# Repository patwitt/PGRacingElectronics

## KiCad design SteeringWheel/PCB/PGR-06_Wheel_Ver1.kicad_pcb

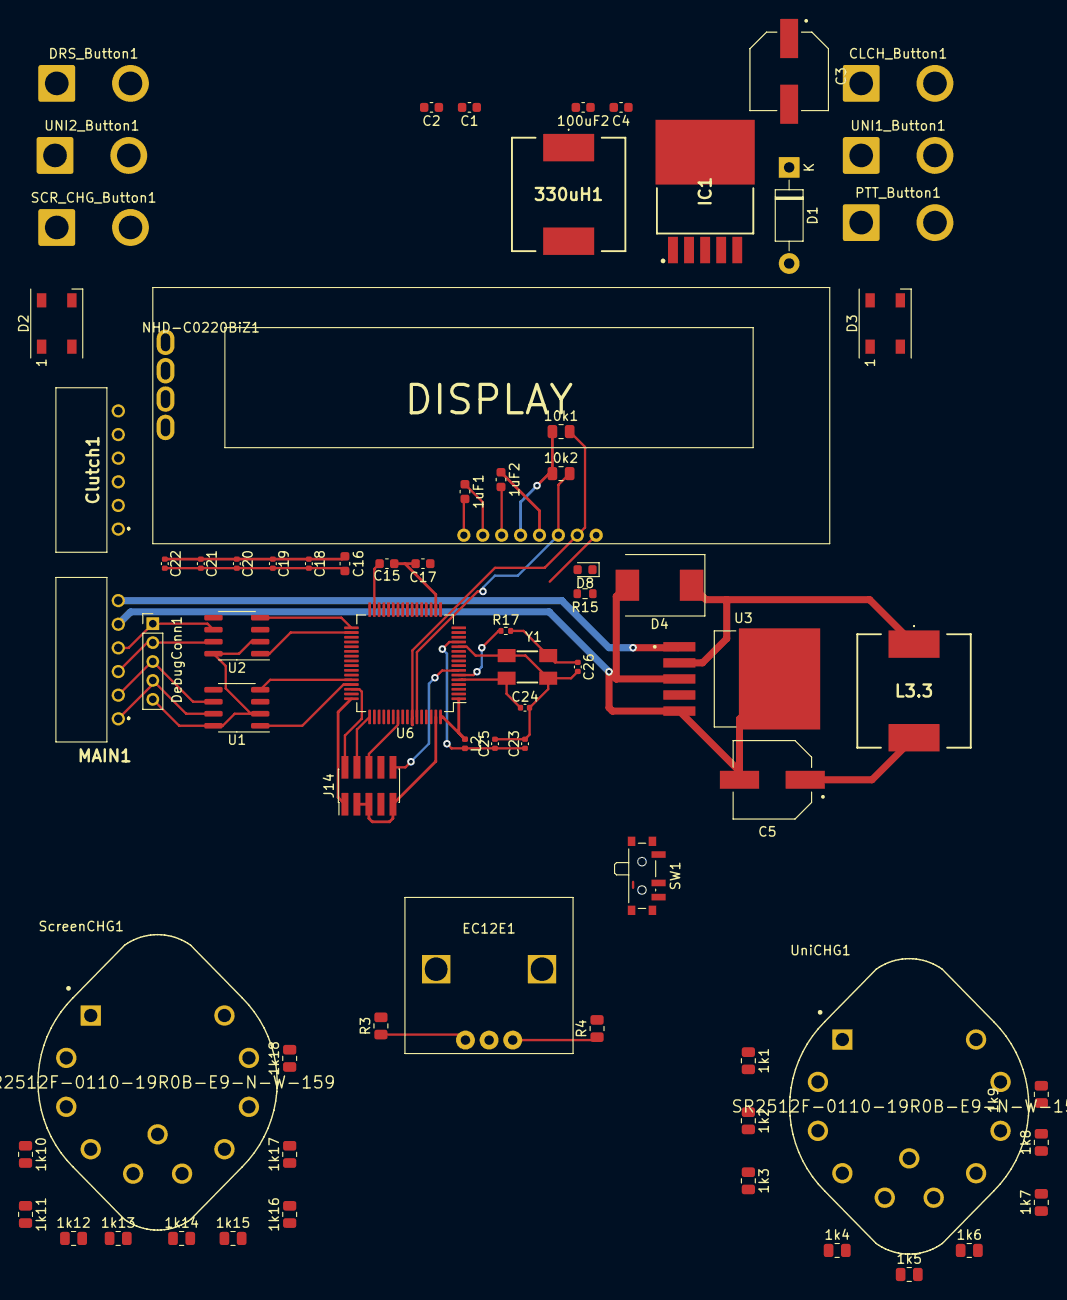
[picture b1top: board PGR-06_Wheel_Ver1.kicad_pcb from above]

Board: 2 copper layers, 73 parts (0 on the bottom side), 59 nets.

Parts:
1k1, 1k2, 1k3, 1k4, 1k5, 1k6, 1k7, 1k8, 1k9, 1k10, 1k11, 1k12, 1k13, 1k14, 1k15, 1k16, 1k17, 1k18: 1k; R_0805_2012Metric
1uF1, 1uF2, 100uF2: C_Small; C_0603_1608Metric
10k1, 10k2: R_Small; R_0805_2012Metric
330uH1: L_Small; 7447707331
C1, C2: C_Small; C_0603_1608Metric
C3, C5: 16SVPG330MX; CAP_16SVPG330MX
C4: 100uF; C_0603_1608Metric
C15, C17: 2u2; C_0603_1608Metric
C16: 4u7; C_0603_1608Metric
C18, C19, C20, C21, C22: 100n; C_0402_1005Metric
C23: 1u; C_0402_1005Metric
C24, C26: 12p; C_0402_1005Metric
C25: 10n; C_0402_1005Metric
CLCH_Button1: SW_Push; SolderWire-2sqmm_1x02_P7.8mm_D2mm_OD3.9mm
Clutch1: 22-05-7065; 22057065
D1: 1N5819; D_DO-41_SOD81_P10.16mm_Horizontal
D2, D3: WS2812B; LED_WS2812B_PLCC4_5.0x5.0mm_P3.2mm
D4: 1N5819; D_SMC
D8: BLUE; LED_0603_1608Metric
DRS_Button1: SW_Push; SolderWire-2sqmm_1x02_P7.8mm_D2mm_OD3.9mm
DebugConn1: Conn_01x05_Male; PinHeader_1x05_P2.00mm_Vertical
EC12E1: EC12E1220405
IC1: LM2575HVS-5.0_NOPB; TO170P1435X465-6N
J14: SWD; PinHeader_2x05_P1.27mm_Vertical_SMD
L2: 39n; L_0402_1005Metric
L3.3: 330uH; 7447707331
MAIN1: 22-05-7065; 22057065
NHD-C0220BiZ1: NHD-C0220BiZ-FS(RGB)-FBW-3VM
PTT_Button1: SW_Push; SolderWire-2sqmm_1x02_P7.8mm_D2mm_OD3.9mm
R3, R4: 10k; R_0805_2012Metric
R15: 1k5; R_0603_1608Metric
R17: 47; R_0402_1005Metric
SCR_CHG_Button1: SW_Push; SolderWire-2sqmm_1x02_P7.8mm_D2mm_OD3.9mm
SW1: SW_SPDT; SW_SPDT_PCM12
ScreenCHG1: SR2512F-0110-19R0B-E9-N-W-159; Alpha_Taiwan-SR2512F-0110-19R0B-E9-N-W-159-MFG
U1, U2: MCP2561-E-SN; SOIC-8_3.9x4.9mm_P1.27mm
U3: LM2575HVS-3.3_NOPB; VREG_TPS79625KTTR
U6: STM32F405RGT6; LQFP-64_10x10mm_P0.5mm
UNI1_Button1, UNI2_Button1: SW_Push; SolderWire-2sqmm_1x02_P7.8mm_D2mm_OD3.9mm
UniCHG1: SR2512F-0110-19R0B-E9-N-W-159; Alpha_Taiwan-SR2512F-0110-19R0B-E9-N-W-159-MFG
Y1: 16MHz; OSCCC500X320X110-4N

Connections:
+3.3VA: C23.1, C25.1, L2.2, U6.13
+3V3: 1k9.2, 1k18.2, 10k1.1, 10k2.1, C5.1, C16.1, C18.1, C19.1, C20.1, C21.1, C22.1, Clutch1.2, J14.1, L2.1, L3.3.2, NHD-C0220BiZ1.5, R3.2, R4.2, SW1.1, ScreenCHG1.10, U3.4, U6.1, U6.19, U6.32, U6.48, U6.64, UniCHG1.10
+5V: 330uH1.1, C1.2, C2.2, C3.1, D2.1, D3.1, IC1.4, U1.3, U2.3
+12V: 100uF2.2, C4.2, IC1.1, MAIN1.6, U3.1
/Rotaries/ENC_A: EC12E1.1, R3.1, U6.42
/Rotaries/ENC_B: EC12E1.3, R4.1, U6.43
/Rotaries/ROT_SCR: ScreenCHG1.11, U6.15, UniCHG1.11
/STM32F405RGT6/BTN_CLCH: CLCH_Button1.2, U6.26
/STM32F405RGT6/BTN_DRS: DRS_Button1.2, U6.28
/STM32F405RGT6/BTN_PTT: PTT_Button1.2, U6.25
/STM32F405RGT6/BTN_SCR: SCR_CHG_Button1.2, U6.24
/STM32F405RGT6/BTN_UNI1: U6.27, UNI1_Button1.2
/STM32F405RGT6/BTN_UNI2: U6.37, UNI2_Button1.2
/STM32F405RGT6/I2C_RESET: NHD-C0220BiZ1.1, U6.57
/STM32F405RGT6/I2C_SCL: 10k1.2, NHD-C0220BiZ1.2, U6.58
/STM32F405RGT6/I2C_SDA: 10k2.2, NHD-C0220BiZ1.3, U6.59
/STM32F405RGT6/LED_DATA: D2.4, U6.39
CAN1_H: DebugConn1.4, MAIN1.1, U1.7
CAN1_L: DebugConn1.3, MAIN1.2, U1.6
CAN1_RX: U1.4, U6.44
CAN1_TX: U1.1, U6.45
CAN2_H: DebugConn1.2, MAIN1.3, U2.7
CAN2_L: DebugConn1.1, MAIN1.4, U2.6
CAN2_RX: U2.4, U6.33
CAN2_TX: U2.1, U6.34
GND: 1k1.1, 1k10.1, 1uF2.1, 100uF2.1, C1.1, C2.1, C3.2, C4.1, C5.2, C15.2, C16.2, C17.2, C18.2, C19.2, C20.2, C21.2, C22.2, C23.2, C24.2, C25.2, C26.2, CLCH_Button1.1, Clutch1.4, Clutch1.6, D1.2, D2.3, D3.3, D4.2, DRS_Button1.1, DebugConn1.5, EC12E1.2, IC1.3, IC1.5, IC1.6, J14.3, J14.5, J14.9, MAIN1.5, NHD-C0220BiZ1.4, PTT_Button1.1, R15.1, SCR_CHG_Button1.1, SW1.3, ScreenCHG1.1, U1.2, U1.8, U2.2, U2.8, U3.3, U3.5, U3.6, U6.12, U6.18, U6.63, UNI1_Button1.1, UNI2_Button1.1, UniCHG1.1, Y1.2, Y1.4
HSE_IN: C24.1, U6.5, Y1.1
HSE_OUT: R17.1, U6.6
LED_STATUS: D8.2, U6.16
NRST: J14.10, U6.7
unnamed: 1k1.2, 1k2.1, UniCHG1.2
unnamed: 1k2.2, 1k3.1, UniCHG1.3
unnamed: 1k3.2, 1k4.1, UniCHG1.4
unnamed: 1k4.2, 1k5.1, UniCHG1.5
unnamed: 1k5.2, 1k6.1, UniCHG1.6
unnamed: 1k6.2, 1k7.1, UniCHG1.7
unnamed: 1k7.2, 1k8.1, UniCHG1.8
unnamed: 1k8.2, 1k9.1, UniCHG1.9
unnamed: 1k10.2, 1k11.1, ScreenCHG1.2
unnamed: 1k11.2, 1k12.1, ScreenCHG1.3
unnamed: 1k12.2, 1k13.1, ScreenCHG1.4
unnamed: 1k13.2, 1k14.1, ScreenCHG1.5
unnamed: 1k14.2, 1k15.1, ScreenCHG1.6
unnamed: 1k15.2, 1k16.1, ScreenCHG1.7
unnamed: 1k16.2, 1k17.1, ScreenCHG1.8
unnamed: 1k17.2, 1k18.1, ScreenCHG1.9
unnamed: 1uF1.1, NHD-C0220BiZ1.7
unnamed: 1uF1.2, NHD-C0220BiZ1.8
unnamed: 1uF2.2, NHD-C0220BiZ1.6
unnamed: 330uH1.2, D1.1, IC1.2
unnamed: C15.1, U6.31
unnamed: C17.1, U6.47
unnamed: C26.1, R17.2, Y1.3
unnamed: D2.2, D3.4
unnamed: D4.1, L3.3.1, U3.2
unnamed: D8.1, R15.2
SWCLK: J14.4, U6.49
SWDIO: J14.2, U6.46
SWO: J14.6, U6.55

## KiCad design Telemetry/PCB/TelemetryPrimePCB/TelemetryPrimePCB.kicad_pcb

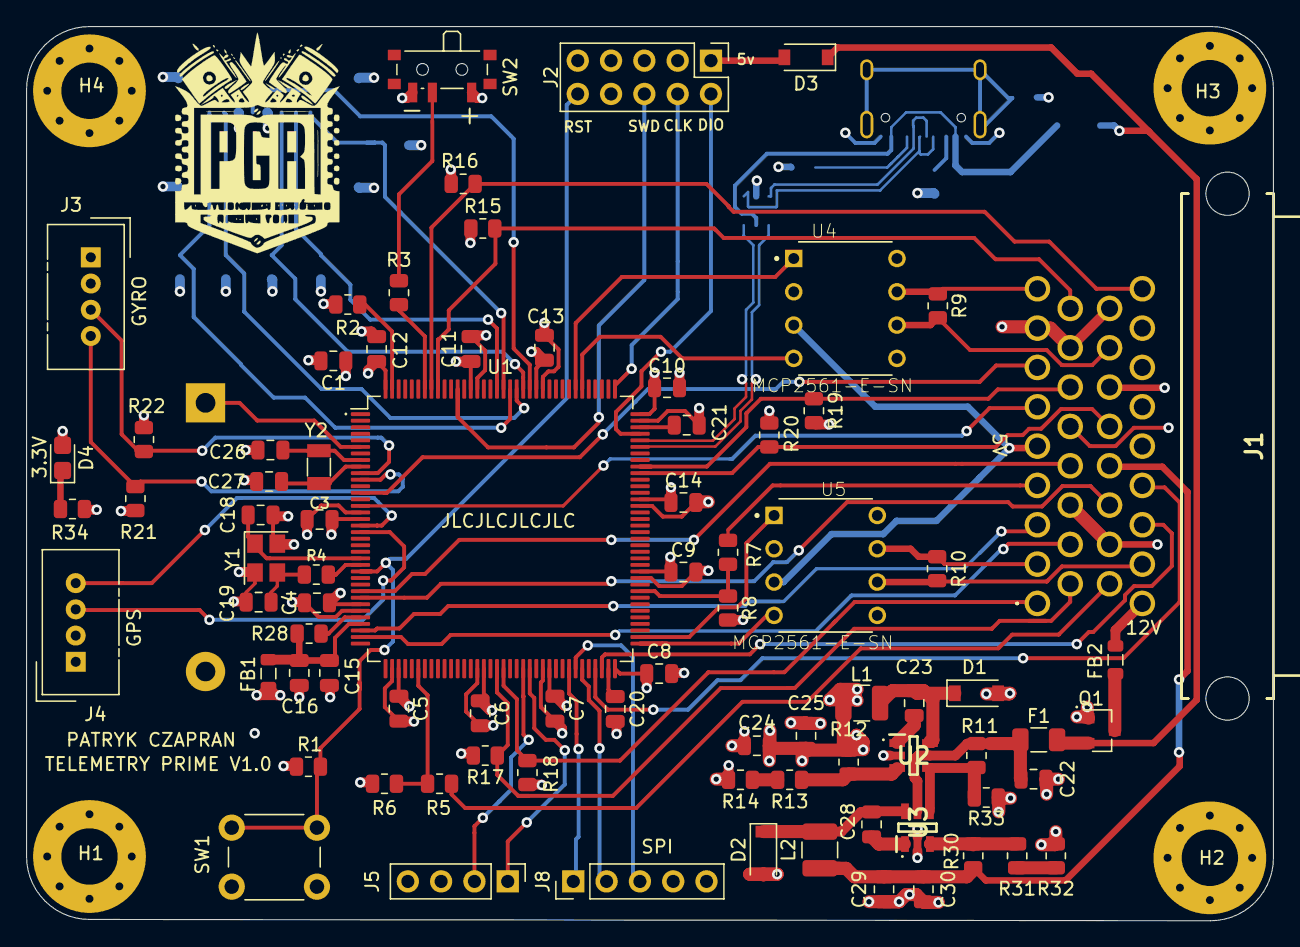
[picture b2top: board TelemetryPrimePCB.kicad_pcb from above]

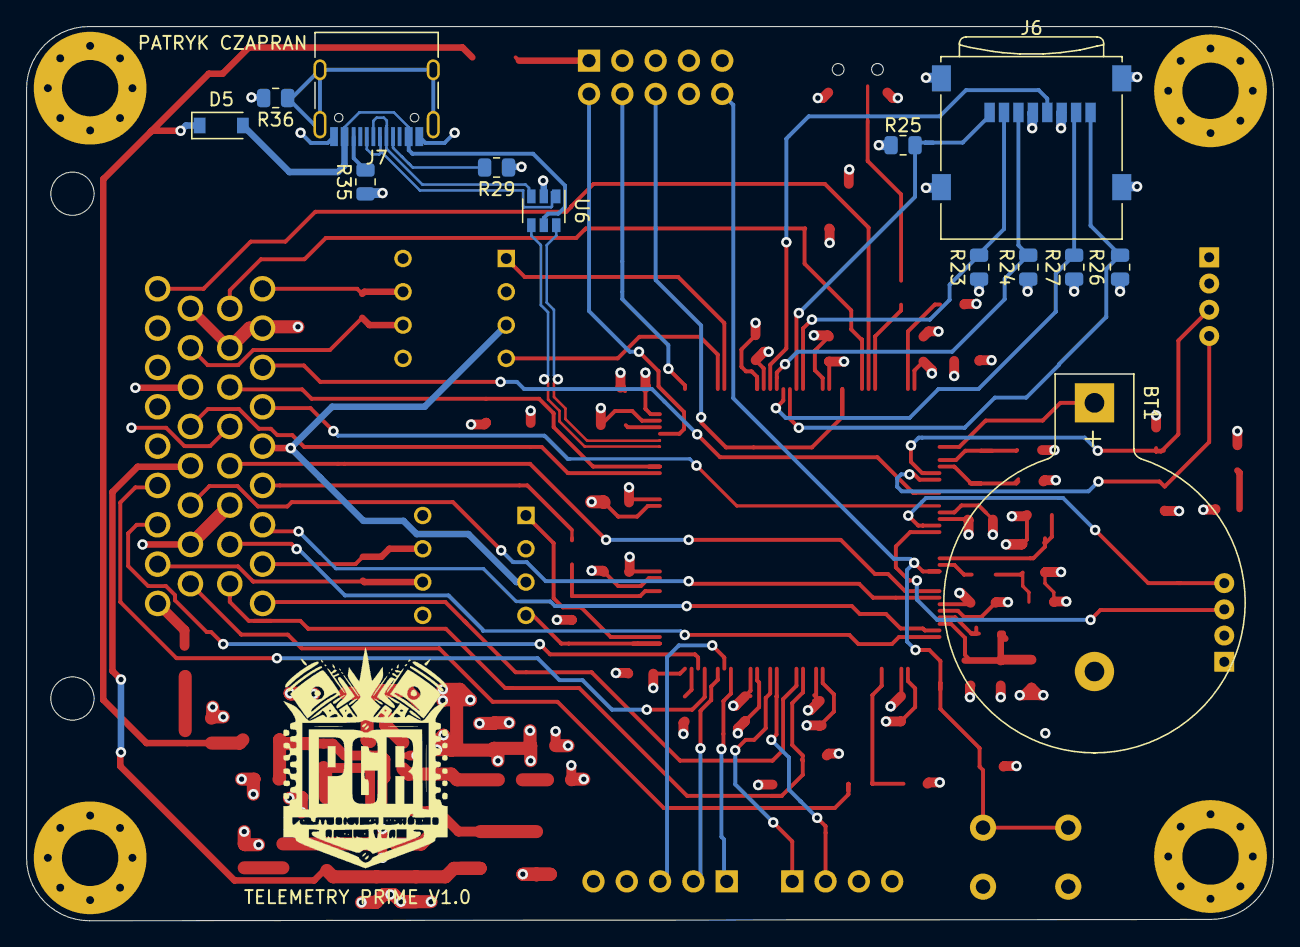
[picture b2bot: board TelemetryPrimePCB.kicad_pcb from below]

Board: 4 copper layers, 95.1 x 68.2 mm, 98 parts (13 on the bottom side), 85 nets.

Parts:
BT1: Battery; BatteryHolder_Keystone_103_1x20mm
C1, C16: 4u7; C_0805_2012Metric
C3, C4, C5, C6, C7, C8, C9, C10, C11, C12, C13, C14, C15: 100n; C_0805_2012Metric
C18, C19: 12p; C_0805_2012Metric
C20, C21: 2u2; C_0805_2012Metric
C22, C24, C25, C29, C30: 10u; C_0805_2012Metric
C23, C28: 10n; C_0805_2012Metric
C26, C27: 6p; C_0805_2012Metric
D1, D2, D3, D5: B230; D_SOD-123
D4: LED; LED_0805_2012Metric_Castellated
F1: 500mA; Fuse_1206_3216Metric
FB1, FB2: Ferrite; L_0805_2012Metric
H1, H2, H3, H4: MountingHole_Pad; MountingHole_4.3mm_M4_Pad_Via
J1: 2-6437285-6; 264372856
J2: Conn_02x05_Odd_Even; PinHeader_2x05_P2.54mm_Vertical
J3: GROOVE(GYRO); NS-Tech_Grove_1x04_P2mm_Vertical
J4: GROOVE(GPS); NS-Tech_Grove_1x04_P2mm_Vertical
J5: Extra UART; PinHeader_1x04_P2.54mm_Vertical
J6: Micro_SD_Card; microSD_HC_Wuerth_693072010801
J7: USB_C_Receptacle_USB2.0; USB_C_Receptacle_HRO_TYPE-C-31-M-12
J8: SPI; PinHeader_1x05_P2.54mm_Vertical
L1, L2: 10u; L_1210_3225Metric
Q1: AO3401A; SOT-23
R1, R2, R3: 10k; R_0805_2012Metric
R4, R28: 47; R_0805_2012Metric
R5, R7, R12, R30: 47K; R_0805_2012Metric
R6, R8, R13: 15K; R_0805_2012Metric
R9, R10: 120; R_0805_2012Metric
R11: 100k; R_0805_2012Metric
R14, R32: 270; R_0805_2012Metric
R15, R16, R17, R18, R19, R20, R21, R22, R23, R24, R25, R26, R27: 4K7; R_0805_2012Metric
R29, R35: 5K11; R_0805_2012Metric
R31: 5K; R_0805_2012Metric
R33: 68K; R_0805_2012Metric
R34: 1K; R_0805_2012Metric
R36: 1M; R_0805_2012Metric
SW1: SW_SPST; SW_PUSH_6mm_H5mm
SW2: SW_SPDT; SW_SPDT_PCM12
U1: STM32F767ZITx; LQFP-144_20x20mm_P0.5mm
U2, U3: MP2359DJ-LF-Z; SOT95P280X145-6N
U4, U5: MCP2561-E-SN; DIP787W45P254L1016H533Q8
U6: USBLC6-2SC6; SOT-23-6
Y1: 25MHz; Crystal_SMD_3225-4Pin_3.2x2.5mm
Y2: LSE 32K; Crystal_SMD_3215-2Pin_3.2x1.5mm

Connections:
5V_STLink: D3.2, J2.1
+3.3VA: C15.1, C16.1, FB1.1, R28.1, U1.33
+3V3: C1.1, C3.1, C4.1, C5.1, C6.1, C7.1, C8.1, C9.1, C10.1, C11.1, C12.1, C13.1, C14.1, C24.2, C25.2, D4.2, FB1.2, J1.23, J3.2, J4.2, J5.4, J6.4, J8.5, L1.2, R1.2, R2.1, R12.1, R15.2, R16.1, R17.2, R18.1, R19.2, R20.1, R21.2, R22.1, R23.1, R24.1, R25.2, R26.2, R27.1, SW2.1, U1.17, U1.30, U1.39, U1.52, U1.62, U1.72, U1.84, U1.95, U1.108, U1.121, U1.131, U1.144
+5V: J1.5, U4.3, U5.3
+5VD: D5.2, J7.A4, J7.A9, J7.B4, J7.B9, U6.5
+8V: C29.2, C30.2, J1.21, L2.2, R30.1
+12V: FB2.1, J1.26
ADC1: J1.3, U1.34
ADC2: J1.11, U1.35
ADC3: J1.13, U1.28
ADC4: J1.20, U1.29
ADC5: J1.7, U1.13
ADC6: J1.6, U1.15
BOOT0: R3.2, U1.138
CAN1_H: J1.9, R9.1, U4.7
CAN1_L: J1.24, R9.2, U4.6
CAN1_RX: U1.114, U4.4
CAN1_TX: U1.115, U4.1
CAN2_H: J1.2, R10.1, U5.7
CAN2_L: J1.27, R10.2, U5.6
CAN2_RX: U1.73, U5.4
CAN2_TX: U1.74, U5.1
D+: J7.A6, J7.B6, U6.1
D-: J7.A7, J7.B7, U6.3
EN: R11.2, R33.1, U2.4, U3.4
GND: BT1.2, C1.2, C3.2, C4.2, C5.2, C6.2, C7.2, C8.2, C9.2, C10.2, C11.2, C12.2, C13.2, C14.2, C15.2, C16.2, C18.2, C19.2, C20.2, C21.2, C22.2, C24.1, C25.1, C26.2, C27.2, C29.1, C30.1, D1.2, D2.2, H1.1, H2.1, H3.1, H4.1, J1.8, J1.12, J1.14, J1.16, J1.19, J1.25, J2.3, J2.5, J2.9, J3.1, J4.1, J5.3, J6.6, J6.9, J7.A1, J7.A12, J7.B1, J7.B12, J8.4, Q1.1, R6.2, R8.2, R14.2, R29.1, R32.2, R33.2, R34.2, R35.1, R36.2, SW1.2, SW2.3, U1.16, U1.31, U1.38, U1.51, U1.61, U1.83, U1.94, U1.107, U1.120, U1.130, U2.2, U3.2, U4.2, U4.8, U5.2, U5.8, U6.2, Y1.2, Y1.4
HSE_IN: C18.1, U1.23, Y1.1
HSE_OUT: R4.1, U1.24
I2C1_CLK: J1.17, R15.1, U1.136
I2C1_SDA: J1.34, R16.2, U1.137
I2C2_CLK: J3.4, R21.1, U1.11
I2C2_SDA: J3.3, R22.2, U1.10
I2C3_CLK: J1.15, R19.1, U1.100
I2C3_SDA: J1.22, R20.2, U1.99
I2C4_CLK: J1.10, R17.1, U1.54
I2C4_SDA: J1.1, R18.2, U1.55
LSE_IN: C26.1, U1.8, Y2.1
LSE_OUT: C27.1, U1.9, Y2.2
NRST: J2.10, R1.1, SW1.1, U1.25
unnamed: C19.1, R4.2, Y1.3
unnamed: C20.1, U1.71
unnamed: C21.1, U1.106
unnamed: C23.1, D1.1, L1.1, U2.6
unnamed: C23.2, U2.1
unnamed: C28.1, D2.1, L2.1, U3.6
unnamed: C28.2, U3.1
unnamed: D3.1, D5.1, F1.2, Q1.2
unnamed: D4.1, R34.1
unnamed: FB2.2, Q1.3
unnamed: J7.A5, R29.2
unnamed: J7.B5, R35.2
unnamed: J7.S1, R36.1
unnamed: R3.1, SW2.2
unnamed: R12.2, R13.1, U2.3
unnamed: R13.2, R14.1
unnamed: R30.2, R31.1, U3.3
unnamed: R31.2, R32.1
PDR_ON: R2.2, U1.143
RP_OUT: C22.1, F1.1, R11.1, U2.5, U3.5
SDMMC_CK: J6.5, U1.122
SDMMC_CMD: J6.3, R24.2, U1.123
SDMMC_D0: J6.7, R27.2, U1.124
SDMMC_D1: J6.8, R26.1, U1.125
SDMMC_D2: J6.1, R25.1, U1.126
SDMMC_D3: J6.2, R23.2, U1.127
SPI_MISO: J8.3, U1.66
SPI_MOSI: J8.2, U1.67
SPI_SCK: J8.1, U1.65
SWCLK: J2.4, U1.109
SWDIO: J2.2, U1.105
SWO: J2.6, U1.133
UART7_RX: J5.2, U1.58
UART7_TX: J5.1, U1.59
USART1_RX: J4.4, U1.18
USART1_TX: J4.3, U1.19
USART2_RX: J1.28, U1.70
USART2_TX: J1.29, U1.69
USB_OTG_D+: U1.104, U6.6
USB_OTG_D-: U1.103, U6.4
VBAT: BT1.1, U1.6
VREFP: R28.2, U1.32
VSS1: J1.4, R7.2
VSS1IN: R7.1, R8.1, U1.81
VSS2: J1.18, R5.1
VSS2IN: R5.2, R6.1, U1.42

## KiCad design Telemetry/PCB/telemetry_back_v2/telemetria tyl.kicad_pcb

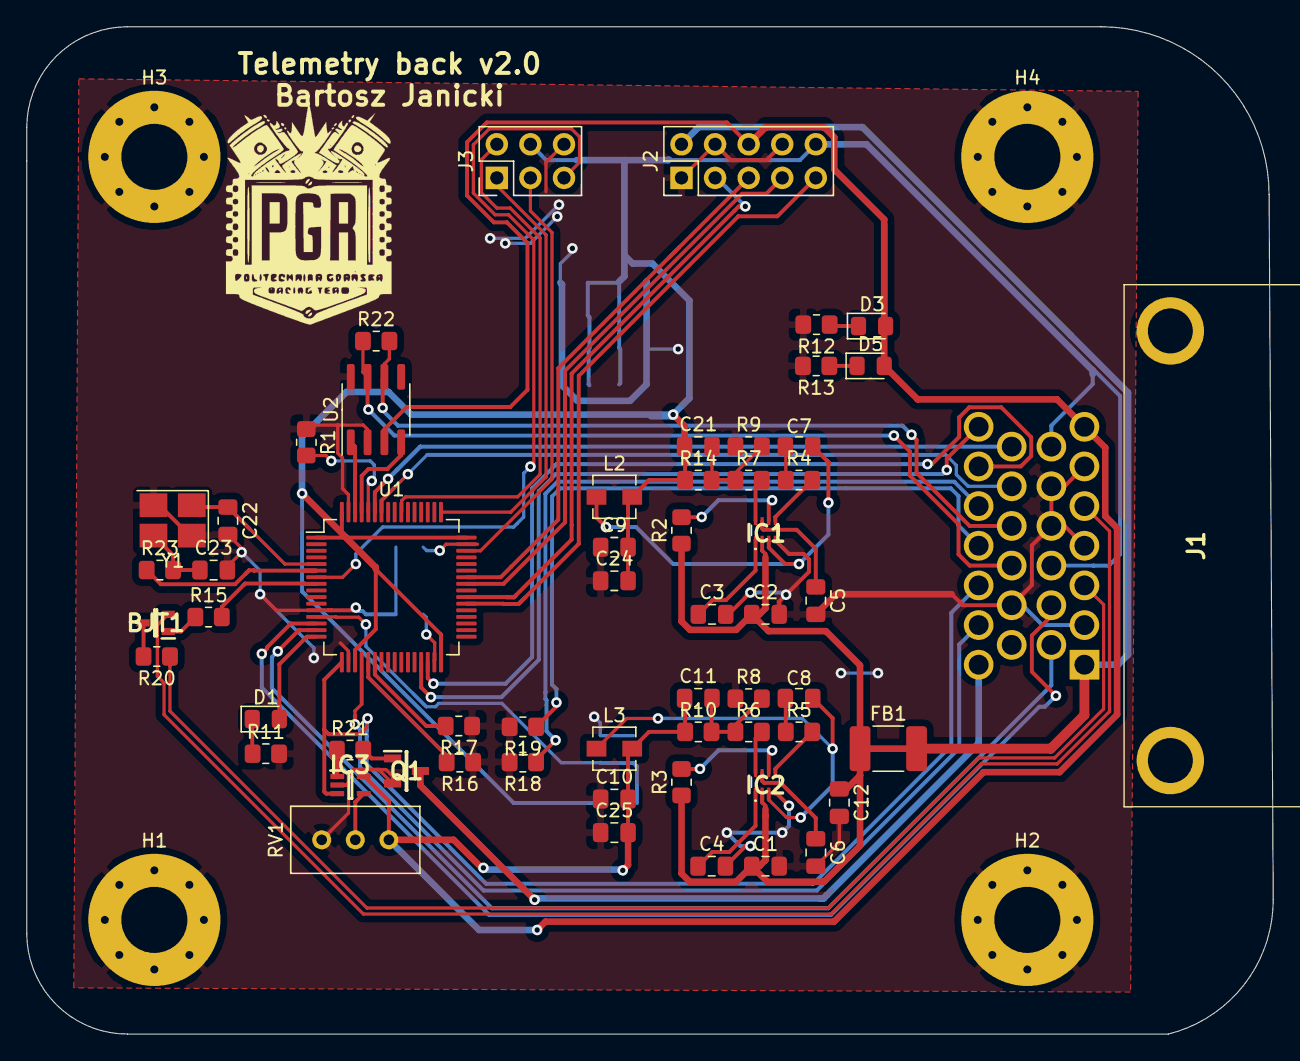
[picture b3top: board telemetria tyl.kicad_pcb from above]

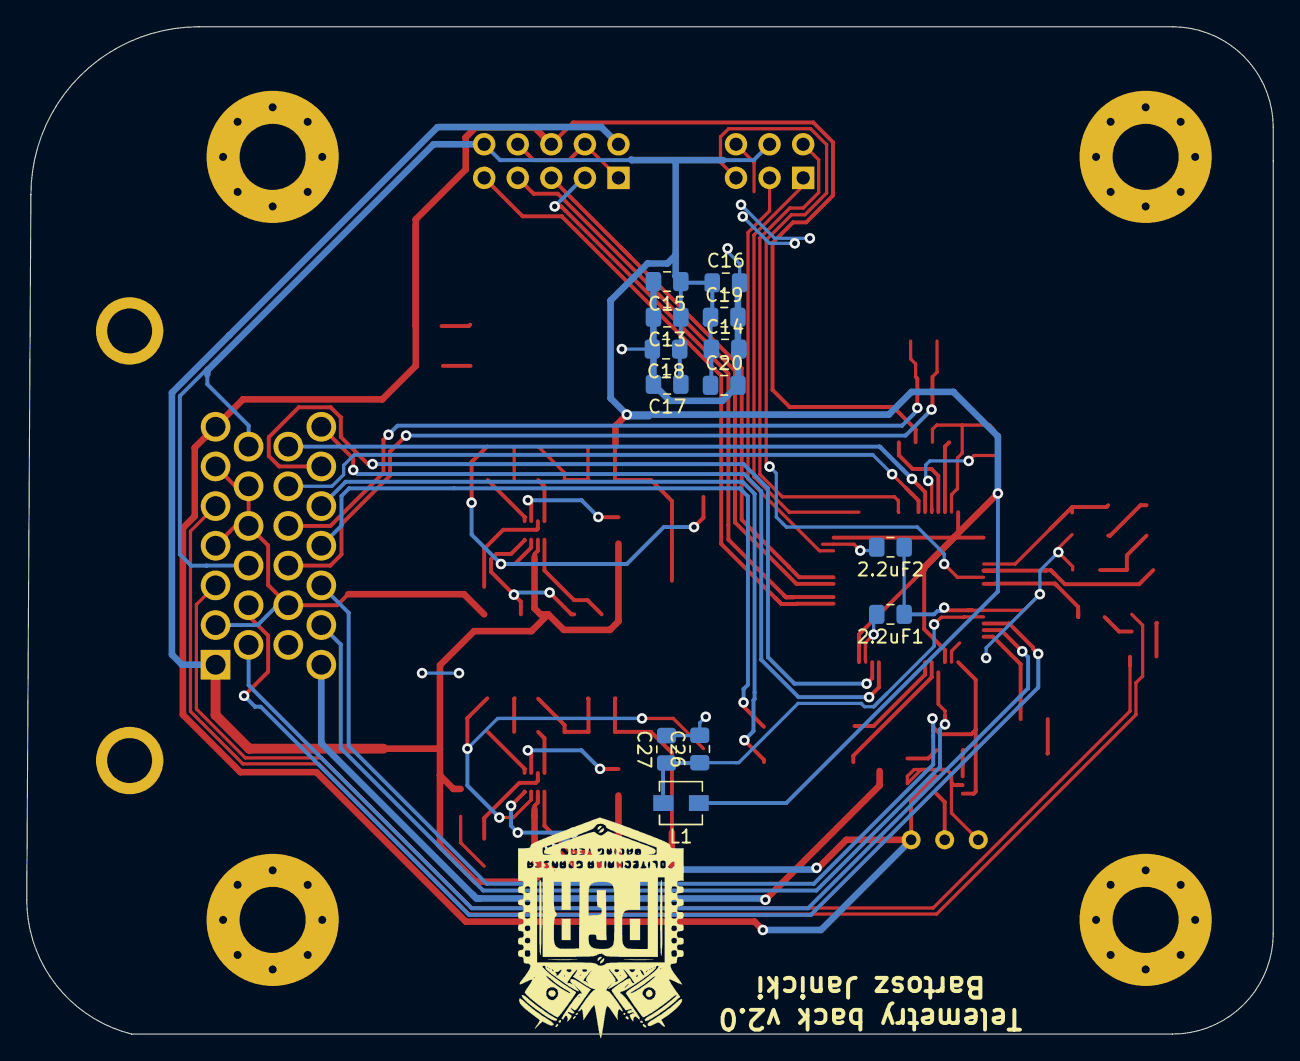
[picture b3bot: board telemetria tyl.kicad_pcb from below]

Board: 2 copper layers, 94.3 x 76.2 mm, 75 parts (13 on the bottom side), 64 nets.

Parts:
2.2uF1, 2.2uF2: C_Small; C_0805_2012Metric_Pad1.18x1.45mm_HandSolder
BJT1: BC846BW,115; SOT65P210X110-3N
C1, C2, C9, C10, C24, C25: 22u; C_0805_2012Metric_Pad1.18x1.45mm_HandSolder
C3, C4: 1n; C_0805_2012Metric_Pad1.18x1.45mm_HandSolder
C5, C6: 6.8n; C_0805_2012Metric_Pad1.18x1.45mm_HandSolder
C7, C8, C26: 1u; C_0805_2012Metric_Pad1.18x1.45mm_HandSolder
C11, C21: 10p; C_0805_2012Metric_Pad1.18x1.45mm_HandSolder
C12, C13, C14, C15, C16, C17, C18, C19, C20: 100nF; C_0805_2012Metric_Pad1.18x1.45mm_HandSolder
C22, C23: 14pF; C_0805_2012Metric_Pad1.18x1.45mm_HandSolder
C27: 10n; C_0805_2012Metric_Pad1.18x1.45mm_HandSolder
D1, D3, D5: LED_3.2V; D_0805_2012Metric_Pad1.15x1.40mm_HandSolder
FB1: Ferrite_Bead; C_1812_4532Metric_Pad1.57x3.40mm_HandSolder
H1, H2, H3, H4: MountingHole_Pad; MountingHole_5mm_Pad_Via
IC1, IC2: MP2331HGTL-P; MP2331HGTLP
IC3: NCX2200GW,125; SOT65P212X110-5N
J1: Conn_01x26_Male; 64734231
J2: Conn_02x05_Odd_Even; PinHeader_2x05_P2.54mm_Vertical
J3: Conn_02x03_Odd_Even; PinHeader_2x03_P2.54mm_Vertical
L1: 39nH; L_Vishay_IHLP-1212
L2: 1.5u; L_Vishay_IHLP-1212
L3: 2.5u; L_Vishay_IHLP-1212
Q1: PMV280ENEAR; SOT95P237X112-3N
R1, R6: 10k; R_0805_2012Metric_Pad1.20x1.40mm_HandSolder
R2, R3: 604k; R_0805_2012Metric_Pad1.20x1.40mm_HandSolder
R4, R5: 20; R_0805_2012Metric_Pad1.20x1.40mm_HandSolder
R7: 20k; R_0805_2012Metric_Pad1.20x1.40mm_HandSolder
R8: 7.68k; R_0805_2012Metric_Pad1.20x1.40mm_HandSolder
R9: 13k; R_0805_2012Metric_Pad1.20x1.40mm_HandSolder
R10, R14: 40.2k; R_0805_2012Metric_Pad1.20x1.40mm_HandSolder
R11: 560; R_0805_2012Metric_Pad1.20x1.40mm_HandSolder
R12, R13: 360; R_0805_2012Metric_Pad1.20x1.40mm_HandSolder
R15: 4.7k; R_0805_2012Metric_Pad1.20x1.40mm_HandSolder
R16, R17: 330; R_0805_2012Metric_Pad1.20x1.40mm_HandSolder
R18, R19, R20: 1k; R_0805_2012Metric_Pad1.20x1.40mm_HandSolder
R21: 3.3k; R_0805_2012Metric_Pad1.20x1.40mm_HandSolder
R22: 120; R_0805_2012Metric_Pad1.20x1.40mm_HandSolder
R23: R_Small; R_0805_2012Metric_Pad1.20x1.40mm_HandSolder
RV1: R_POT; Vishay_pot
U1: STM32F405RGTx; LQFP-64_10x10mm_P0.5mm
U2: MCP2561-E-SN; SOIC-8_3.9x4.9mm_P1.27mm
Y1: 16Mhz; Crystal_SMD_3225-4Pin_3.2x2.5mm_HandSoldering

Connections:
+3.3VA: C26.1, C27.1, L1.2, U1.13
+3V3: C9.2, C13.1, C14.1, C15.1, C16.1, C17.1, C18.1, C19.1, C20.1, C21.1, C24.2, J1.8, J1.11, J2.10, J3.4, L1.1, L2.2, R14.1, U1.1, U1.19, U1.32, U1.48, U1.64
+5V: C10.2, C11.1, C25.2, D3.2, D5.2, IC3.5, J1.7, J2.6, L3.2, R10.1, RV1.3, U2.3
+12V: C1.1, C2.1, C12.1, FB1.1, FB1.2, IC1.2, IC2.2, J1.1, J2.2, R2.1, R3.1
ADC1_IN0_AMORKI: J1.12, U1.14
ADC2_IN1_AMORKI: J1.13, U1.15
Additional_1: J2.9, U1.38
Additional_2: J2.3, U1.39
Additional_PWM_1: J2.7, U1.41
Additional_PWM_2: J2.5, U1.42
BREAK_PRESSURE_0: IC3.3, J1.24, U1.17
BREAK_PRESSURE_ADC: J1.25, U1.20
CAN1_RX: U1.61, U2.4
CAN1_TX: U1.62, U2.1
CAN_H1: J1.16, R22.1, U2.7
CAN_L1: J1.17, R22.2, U2.6
FB_1: IC1.8, R7.2
FB_2: IC2.8, R6.2
GND: 2.2uF1.1, 2.2uF2.1, C1.2, C2.2, C3.2, C4.2, C5.2, C6.2, C9.1, C10.1, C12.2, C13.2, C14.2, C15.2, C16.2, C17.2, C18.2, C19.2, C20.2, C22.2, C23.2, C24.1, C25.1, C26.2, C27.2, H1.1, H2.1, H3.1, H4.1, IC1.4, IC2.4, IC3.2, J1.2, J1.4, J1.6, J1.9, J1.10, J1.15, J2.1, J2.4, J2.8, J3.6, Q1.2, R1.1, R8.1, R9.1, R11.2, R12.2, R13.2, R16.1, R17.1, R18.2, R19.2, RV1.1, U1.12, U1.18, U1.63, U2.2, U2.8, Y1.2, Y1.4
GND_MIC&ANC: J1.3, R20.1
GND_SPK: BJT1.2, J1.5
I2C1_SCL: J1.18, U1.58
I2C1_SDA: J1.19, U1.59
I2C2_SCL: J1.20, U1.29
I2C2_SDA: J1.21, U1.30
LED_GND: J1.26, Q1.3
LED_STATUS: D1.2, U1.16
NRST: J3.5, U1.7
unnamed: 2.2uF1.2, U1.31
unnamed: 2.2uF2.2, U1.47
unnamed: BJT1.1, R15.1
unnamed: BJT1.3, R20.2
unnamed: C3.1, IC1.1
unnamed: C4.1, IC2.1
unnamed: C5.1, IC1.7
unnamed: C6.1, IC2.7
unnamed: C7.2, R4.1
unnamed: C8.2, R5.1
unnamed: C11.2, R6.1, R8.2, R10.2
unnamed: C21.2, R7.1, R9.2, R14.2
unnamed: C23.1, R23.2, Y1.3
unnamed: D1.1, R11.1
unnamed: D3.1, R12.1
unnamed: D5.1, R13.1
unnamed: IC1.5, R4.2
unnamed: IC1.6, R2.2
unnamed: IC2.5, R5.2
unnamed: IC2.6, R3.2
unnamed: IC3.1, R21.1
unnamed: IC3.4, RV1.2
unnamed: Q1.1, R21.2
unnamed: R1.2, U1.60
PTT: R15.2, U1.8
RCC_OSC_IN: C22.1, U1.5, Y1.1
RCC_OSC_OUT: R23.1, U1.6
SWCLK: J3.1, U1.49
SWDIO: J3.3, U1.46
SWO: J3.2, U1.55
SW_1: C7.1, IC1.3, L2.1
SW_2: C8.1, IC2.3, L3.1
TIM2_ETR: R16.2, U1.21
TIM3_ETR: R17.2, U1.22
VSS_IN_1: J1.22, R18.1
VSS_IN_2: J1.23, R19.1
